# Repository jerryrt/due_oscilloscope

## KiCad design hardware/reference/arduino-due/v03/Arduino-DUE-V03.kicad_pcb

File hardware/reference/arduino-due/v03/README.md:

# Arduino Due V03 in KiCad

Open **[Arduino-DUE-V03.kicad_pro](Arduino-DUE-V03.kicad_pro)** in the
**KiCad 10 Project Manager**, then double-click `Arduino-DUE-V03.kicad_pcb`
in the project tree. You can also open the
[PCB](Arduino-DUE-V03.kicad_pcb) directly in the PCB Editor.
This is the working Due reference for the
owner's board. The alternate [V02g board](../v02g/DUE_V02g.kicad_pcb)
is retained for comparison.

The owner reported DUE R3 silkscreen, an AMS1117 regulator, a separate
inductor and a six-pin IC2 on 2026-11-01. That matches V03's power-supply
topology rather than V02g's IC5 module. The source specifies NCP1117 at
IC4; AMS1117 is a reported substitution, and IC2's exact marking is
unreported. [Observation record](../hardware-observations.json).

The source is `Arduino-DUE-V03`, retained as the original extracted EAGLE
[PCB](source/Arduino-DUE-V03.brd) and [schematic](source/Arduino-DUE-V03.sch).
Download ZIPs are intentionally omitted; their original names and hashes
remain in `sources.json`. Original publisher notices remain in these
source files. This is a local conversion, not an Arduino-published native
KiCad design.

| File | Purpose |
|---|---|
| `Arduino-DUE-V03.kicad_pro` | Project entry point and shared settings; initialized from KiCad 10.0.6's default template |
| `Arduino-DUE-V03.kicad_pcb` | Full converted PCB with embedded 2D footprints |
| `Arduino-DUE-V03.kicad_dru` | Importer-generated rules, not a fully verified project setup |
| `source/Arduino-DUE-V03.brd` | Unmodified EAGLE PCB |
| `source/Arduino-DUE-V03.sch` | Unmodified EAGLE schematic; no native KiCad schematic conversion |
| `sources.json` | Archive provenance, file hashes and layer-recovery notes |
| `import-report.json` | KiCad import statistics and diagnostics |
| `validation.json` | Source correspondence, reload and SVG-export checks |
| `import-board.py` / `check-board.py` | Recreate the board / verify it |

The PCB was originally imported in standalone mode, which did not create
a project file. The added `.kicad_pro` uses the same basename as the PCB
so KiCad opens them together. It starts with KiCad defaults; fabrication
rules and source net-class constraints have not been qualified. The
importer-generated `.kicad_dru` remains alongside it. Reimporting the board
preserves the project file and its settings.

The `.kicad_prl` file is local editor/view state and is ignored by Git.
There is still no native `.kicad_sch`; the original EAGLE schematic is
retained under `source/`. Creating a project file does not convert it.

KiCad **10.0.6** imports all **129 source components**, plus six footprints
for standalone mounting holes. All **591 source pad-to-net assignments**
match, and all component positions match within 0.000002 mm. Sixteen
references without numeric suffixes gain a trailing `0`; `validation.json`
records the mapping. Native load/save/reload and top-layer SVG export pass.
The import report contains no warnings or errors.

The importer puts seven unique straight-line restriction geometries on
an invalid `UNDEFINED` layer, merging front/back duplicates. The script
recovers all ten source lines as reference drawings: five front lines on
`User.1`, five back lines on `User.2`. **These lines do not enforce copper
keepouts.** Imported circular rule areas are separate. This board is for
reference and inspection; it has not been qualified for fabrication.
The owner's power-layout observations support using it as the reference;
full-board geometry and electrical continuity remain to be checked physically.

## The analog reference network (AREF, ADVREF)

Read from `Arduino-DUE-V03.kicad_pcb` (the same nets are in the EAGLE schematic).
`tests/test_due_reference_network.py` holds this table to the PCB. It is the
converted board file, not the owner's physical board: check continuity before
reworking anything.

| Net | Pads on it |
|---|---|
| `AREF` | BR1 pad 1, and the AREF header pin (header `PWMH0` pad 8). Nothing else |
| `AVREFL` | BR1 pad 2, JR1 pad 2, C34 (100 nF to ground), L3 pad 1 |
| `AVREF` | L3 pad 2, C19 (100 nF to ground), the SAM3X's ADVREF pin (U1 pad 75) |
| `+3V3` | BR1 pad 3, JR1 pad 1, and the rest of the 3.3 V rail |

L3 is the ferrite bead `MH2029-300Y` in an 0805, which by its part number is 30
ohms at 100 MHz *(check)*. BR1 is the 0402 three-pad jumper `J0402`, not mounted,
on the top copper layer, with 1.3 mm between pad centres. JR1 is a 0 ohm 0402 on
the top layer.

**As shipped,** JR1 joins 3.3 V to `AVREFL`, and the converters' reference is
3.3 V through L3 and C19. The AREF header pin goes nowhere.

**To drive ADVREF from outside,** in this order. The AFE requirement decided D6 as
measure only, so this is a later option, not part of the AFE's version 1:

1. Remove JR1.
2. Bridge BR1 pads 1 and 2: a 0402 0 ohm part fits the footprint, and a solder
   bridge across the gap of 0.6 mm (pads 0.7 mm long on a 1.3 mm pitch) also reaches, with less margin. The AREF header pin is then
   `AVREFL`, and ADVREF follows it through L3.
3. Check continuity before power: AREF to ADVREF closed, 3.3 V to AREF open.

**The order matters.** With BR1 pads 1 and 2 bridged and JR1 still fitted, the
AREF pin is tied to the 3.3 V rail through 0 ohms, and whatever drives AREF is
shorted to it.

Both parts are on the top layer under where a shield sits, so the rework is done
before stacking. A shield reaches AREF through the stacking header, with no jumper
wire. On the Due it is header `PWMH0` pad 8 in this board file, the AREF pin of
the header.

**The load an external reference sees:** C34, then the bead, then C19, about 200 nF,
before any trace and header contact on the shield. It has to be stable with that
and with the converters' switching load, a datasheet check. A Due reworked this way
and run without a reference connected has a floating ADVREF.

**Without touching JR1,** or with a way back:

- **Do not drive ADVREF.** Leave the Due stock and let the ADC read the shield's
  reference as an input. That gives each board's absolute gain and its drift to the
  host, and needs no rework; it does not quieten ADVREF.
- **Use BR1 as the selector it was drawn as.** Remove JR1 once, then bridge BR1 pads
  2 and 3 for the stock behaviour (3.3 V to AVREFL, the same connection JR1 made) or
  pads 1 and 2 for an external reference. With 2 and 3 bridged the Due works alone
  and a shield driving AREF cannot hurt it. With 1 and 2 bridged and no reference
  connected, ADVREF has no source, and the converters do not work.
- **Rework one Due only,** and keep it with the shield. The others stay stock, which
  also gives a control.

Removing JR1 and leaving BR1 open does leave ADVREF with no source: the only paths
into `AVREFL` and `AVREF` are JR1 and BR1.

Not established by the board file: the highest ADVREF the SAM3X accepts against its
analog supply `VDDANA` (3.3 V through a second bead, L1), a datasheet check.

## 3D view

**119 component models are assigned.** The owner-supplied STEP assembly provides 18:
the MCU, both USB connectors, barrel jack, main headers, debug/SPI/ICSP/JTAG
headers, two large capacitors and reset switch. Another 91 assignments use
standard KiCad package bodies, and 10 use documented simplified bodies for
the fuses, power inductor, small crystal, ESD protectors and erase switch.
Reopen the PCB from disk
and choose **View -> 3D Viewer** (Option+3 on macOS).

The owner reported on 2026-11-01 that the initial 18-model preview passed a first visual
inspection and matches the physical board well. This is an overall visual
check, with no dimensional measurements or electrical checks reported.
The expanded population shown above has not yet been inspected by the owner.
[Observation record](../hardware-observations.json).

The source board is 101.6 x 53.34 mm and its six mounting-hole centers
match V03's EAGLE source within 0.000006 mm. Bodies retain the source's
small placement offsets, including the MCU's 0.020 mm center offset.
These are CAD correspondence checks, not physical measurements. Connector
heights, detailed pin fit and component substitutions are not qualified.

The supplied assembly's PCB slab is excluded so the native PCB and copper
remain visible. Its oversized LED bodies and generic capacitor bodies are
also excluded; standard package and simplified bodies now fill the small
components. Four bare fiducials and six source NM items (including BR1)
remain without bodies. Generic
plastic/metal colors improve visibility; they do not identify actual
materials or capacitor values. New package models align polarity and pin-1
to the source pad layout; installed markings and body heights remain
unqualified. In particular the tantalum B-case bodies and erase-switch
height are approximations. The
[model preparation/alignment record](../models/README.md) lists all assets
and exclusions. [Attachment evidence](models-3d.json) confirms every
non-model line of the PCB file is unchanged.

`attach-models.py` restores these assignments without rewriting the native
geometry. `import-board.py` also reapplies them when `models/alignment.json`
is present. The checker verifies all assigned file paths and hashes.

From the repository root, recreate the conversion (overwrites this V03
PCB and its import/provenance records):

```sh
python3 hardware/reference/arduino-due/v03/import-board.py
```

Then verify with KiCad's bundled Python on this Mac:

```sh
/Applications/KiCad/KiCad.app/Contents/Frameworks/Python.framework/Versions/3.9/bin/python3 hardware/reference/arduino-due/v03/check-board.py
```

On another system use Python with KiCad 10's `pcbnew` module available.
Set `KICAD_CLI` if the executable is not on PATH or at the default macOS
location. The checker writes `validation.json` and uses temporary files
for its reload and SVG checks.

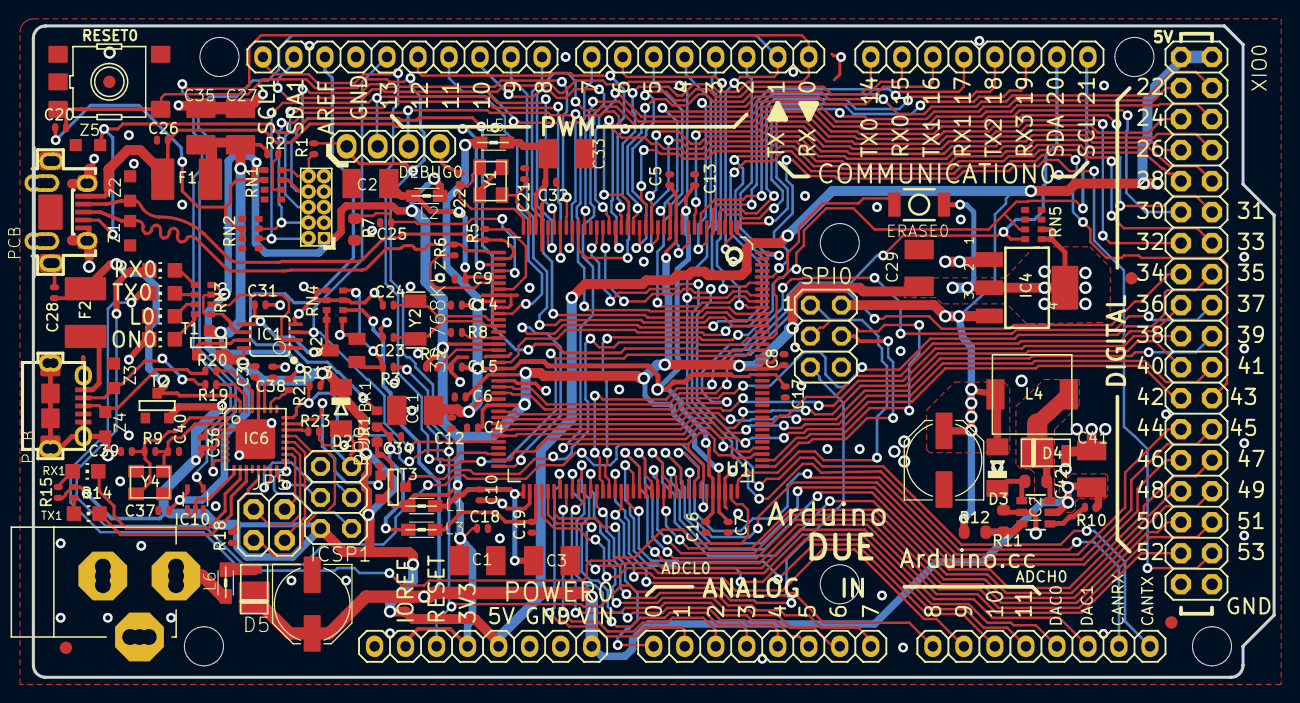
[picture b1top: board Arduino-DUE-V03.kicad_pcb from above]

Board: 2 copper layers, 101.6 x 53.3 mm, 135 parts (0 on the bottom side), 150 nets.

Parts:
ADCH0: 8x1F-H8.5; 1X08
ADCL0: 8x1F-H8.5; 1X08
BR1: NM; J0402
C1, C2, C3, C11, C27, C29, C33, C35, C41: 10u; SMC_B
C4, C5, C6, C7, C8, C9, C10, C12, C13, C14, C15, C16, C17, C18, C19, C28, C30, C31, C32, C34, C36, C37: 100n; C0402
C20, C26: 10n; C0402
C21, C22, C25, C39, C40: 22p; C0402
C23, C24: 22pF_NM; C0402
C38: 1u; C0402
C42: 10n; C0603-ROUND
COMMUNICATION0: 8x1F-H8.5; 1X08
D2, D3: CD1206-S01575; MINIMELF
D4, D5: SS1P3L; DO220AAL
DEBUG0: STRIP 4x1V M; 1X04
ERASE0: SMD_157SW
F1, F2: MF-MSMF050-2 500mA; L1812
FID1, FID2, FID3, FID4: FIDUCIALMOUNT; FIDUCIA-MOUNT
IC1: LMV358IDGKR; MSOP08
IC2: LM2734Y; SOT23-6
IC4: NCP1117ST33T3G -3V3; SOT223
IC6: ATMEGA16U2-MU; MLF32
IC10: 74LVC1G125DCK; SC70-5
ICSP1: 3x2M; 2X03
J3: USB-MICRO B; CON2_USB_MICRO_B_AT
JP5: 2x2M - NM; 2X02
JR1: 0R; R0402
JTAG0: PINHEAD_2X05_127
L0: YELLOW; CHIP-LED0805
L1, L2, L3, L5, L6: MH2029-300Y; 0805
L4: 10u SRR0604-100ML; SRR0604
ON0: GREEN; CHIP-LED0805
PC1, PC2: 47u; PANASONIC_D
POWER0: 8x1F-H8.5; 1X08
PWMH0: 10x1F-H8.5; 1X10
PWML0: 8x1F-H8.5; 1X08
Q2: BC847BSMD; SOT23
R1: 0R; R0402
R2, R13, R18, R99: 10K; R0402
R3, R14, R15, R21, R23: 1K; R0402
R4: 100K; R0402
R5, R6: 39R 1%; R0402
R7: 6k8 1%; R0603-ROUND
R8: 0R_NM; R0402
R9: 1M_NM; R0402
R10: 10k; R0402
R11: 10K; R0603-ROUND
R12: 52K3; R0603-ROUND
R19, R20: 22R; R0402
RESET0: TS42
RN1, RN2, RN4: 100K; CAT16
RN3: 1k; CAY16
RN5: 1K5; CAT16
RX0, RX1: YELLOW; CHIP-LED0805
SPI0: 3x2M; 2X03
T1, T2, T3: FDN340P; SOT-23
TX0, TX1: YELLOW; CHIP-LED0805
U1: ATSAM3X8EA-AU; LQFP144
UNK_HOLE_0: dummyfp0
UNK_HOLE_1: dummyfp1
UNK_HOLE_2: dummyfp2
UNK_HOLE_3: dummyfp3
UNK_HOLE_4: dummyfp4
UNK_HOLE_5: dummyfp5
USB1: MICRO-USB-AB1; MCR-AB1-S-RA-SMT
X2: POWERSUPPLY_DC21MMX; POWERSUPPLY_DC-21MM
XIO0: 18x2F-H8.5; 2X18
Y1: 12MHz KX-7 20pF; CRYSTAL-3.2-2.5
Y2: 32.768Khz; RESONATOR_EPSON_FC_145
Y4: 16MHz KX-7 20pF; CRYSTAL-3.2-2.5
Z1, Z2, Z3, Z4, Z5: CG0603MLC-05E; CT_CN0603

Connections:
8PB4: IC6.18, JP5.1
8PB5: IC6.19, JP5.3
8PB6: IC6.20, JP5.2
8PB7: IC6.21, JP5.4
16U2-TX: IC6.9, IC10.1, IC10.2
+3V3: BR1.3, C1.+, C4.2, C5.2, C6.2, C7.2, C8.2, C18.2, C20.2, C29.+, C37.1, ERASE0.1, IC1.6, IC4.2, IC4.4, IC10.5, JR1.1, JTAG0.1, L1.1, L2.1, POWER0.2, POWER0.4, R4.2, R99.2, RN1.5, RN1.6, RN2.2, RN2.3, RN3.5, RN3.7, RN3.8, RN5.1, RN5.2, T3.2, U1.11, U1.52, U1.57, U1.62, U1.105, U1.125
+5V: C30.2, C36.1, D2.C, D3.A, IC1.8, IC4.3, IC6.4, IC6.32, ICSP1.2, L4.P$2, PC2.+, POWER0.5, R12.1, R13.2, R14.1, R15.1, SPI0.2, T1.2, T2.2, XIO0.1, XIO0.2
AD0: ADCL0.1, U1.78
AD1: ADCL0.2, U1.79
AD2: ADCL0.3, U1.80
AD3: ADCL0.4, U1.81
AD4: ADCL0.5, U1.82
AD5: ADCL0.6, U1.83
AD6: ADCL0.7, U1.84
AD7: ADCL0.8, U1.85
AD8: ADCH0.1, U1.88
AD9: ADCH0.2, U1.89
AD10: ADCH0.3, U1.90
AD11(TXD3): ADCH0.4, U1.91
AD14(RXD3): U1.92, XIO0.33
AREF: BR1.1, PWMH0.8
AVREF: C19.2, L3.2, U1.75
AVREFL: BR1.2, C34.2, JR1.2, L3.1
BD+: J3.P3, R20.2, Z4.2
BD-: J3.P2, R19.2, Z3.2
BOOST: C42.1, D3.C, IC2.1
CANRX0: ADCH0.7, U1.24
CANTX0: ADCH0.8, U1.23
CANTX1/IO: U1.140, XIO0.34
CMP: C31.2, IC1.5, Q2.3, RN4.3, RN4.4
D+: R6.1, U1.37, USB1.3, Z1.1
D-: R5.1, U1.38, USB1.2, Z2.1
DAC0(CANRX1): ADCH0.5, U1.76
DAC1: ADCH0.6, U1.77
DTR: IC6.13, R18.1
EN: IC2.4, R10.2
ERASE_CMD: IC6.23, R99.1, T3.3
ERASE_S: ERASE0.2, T3.1, U1.130
FB: IC2.3, R11.1, R12.2
GATE_CMD: IC1.7, T1.3
GND: C1.-, C2.-, C3.-, C4.1, C5.1, C6.1, C7.1, C8.1, C9.1, C10.1, C11.-, C12.1, C13.1, C14.1, C15.1, C16.1, C17.1, C18.1, C19.1, C21.2, C22.2, C23.2, C24.2, C25.2, C26.2, C27.-, C28.2, C29.-, C30.1, C31.1, C32.1, C33.-, C34.1, C35.-, C36.2, C37.2, C38.2, C39.2, C40.2, C41.-, D4.P$2, DEBUG0.1, IC1.4, IC2.2, IC4.1, IC6.3, IC6.28, IC6.33, IC10.3, ICSP1.6, J3.P5, J3.P$1, J3.P$2, J3.P$3, J3.P$4, J3.P$5, J3.P$6, J3.P$7, J3.P$8, J3.S1, J3.S2, J3.S3, J3.S4, J3.S5, J3.S6, JTAG0.3, JTAG0.5, JTAG0.9, L0.C, ON0.C, PC1.-, PC2.-, POWER0.6, POWER0.7, PWMH0.7, Q2.2, R2.1, R7.1, R8.1, R11.2, R18.2, RESET0.1, RESET0.2, RN1.1, RN1.2, RN1.7, RN1.8, RN2.1, RN2.4, RN2.5, RN2.8, RN4.1, RN4.2, RN4.5, RN4.7, SPI0.6, T2.3, U1.12, U1.33, U1.44, U1.46, U1.54, U1.58, U1.74, U1.106, U1.126, USB1.5, USB1.P$1, USB1.P$2, USB1.P$3, USB1.P$4, USB1.P$5, USB1.P$6, USB1.P$7, USB1.P$8, USB1.P$9, USB1.P$10, USB1.P$11, USB1.S1, USB1.S2, USB1.S3, USB1.S4, X2.1, X2.3, XIO0.35, XIO0.36, Y1.2, Y1.4, Y4.2, Y4.4, Z1.2, Z2.2, Z3.1, Z4.1, Z5.1
JTAG_RESET: JTAG0.10, R1.1, RN1.4
JTAG_TCK: DEBUG0.2, JTAG0.4, RN2.7, U1.28
JTAG_TDI: JTAG0.8, RN1.3, U1.29
JTAG_TDO: JTAG0.6, U1.30
JTAG_TMS: DEBUG0.3, JTAG0.2, RN2.6, U1.31
L13: IC1.1, IC1.2, RN3.6
MASTER-RESET: C20.1, DEBUG0.4, POWER0.3, R1.2, R23.2, RESET0.3, RESET0.4, SPI0.5, U1.47
MISO: SPI0.1, U1.108
MISO2: IC6.17, ICSP1.1
MOSI: SPI0.4, U1.109
MOSI2: IC6.16, ICSP1.4
unnamed: IC6.26, R21.1
unnamed: L0.A, RN3.3
unnamed: ON0.A, RN3.4
unnamed: R15.2, RX1.A
unnamed: R8.2, U1.51
unnamed: Q2.1, R3.2, RN4.8
unnamed: R4.1, U1.53
unnamed: D5.P$2, L6.1
unnamed: R5.2, U1.43
unnamed: R6.2, U1.42
unnamed: R14.2, TX1.A
unnamed: RN3.1, RX0.A
unnamed: RN3.2, TX0.A
PIN22: U1.1, XIO0.3
PIN23: U1.7, XIO0.4
PIN24: U1.8, XIO0.5
PIN25: U1.13, XIO0.6
PIN26: U1.14, XIO0.7
PIN27: U1.15, XIO0.8
PIN28: U1.16, XIO0.9
PIN29: U1.19, XIO0.10
PIN30: U1.22, XIO0.11
PIN31: U1.26, XIO0.12
PIN32: U1.32, XIO0.13
PIN33: U1.55, XIO0.14
PIN34: U1.59, XIO0.15
PIN35: U1.60, XIO0.16
PIN36: U1.116, XIO0.17
PIN37: U1.63, XIO0.18
PIN38: U1.64, XIO0.19
PIN39: U1.65, XIO0.20
PIN40: U1.66, XIO0.21
PIN41: U1.67, XIO0.22
PIN42: U1.71, XIO0.23
PIN43: U1.72, XIO0.24
PIN44: U1.101, XIO0.25
PIN45: U1.100, XIO0.26
PIN46: U1.99, XIO0.27
PIN47: U1.98, XIO0.28
PIN48: U1.97, XIO0.29
PIN49: U1.96, XIO0.30
PIN50: U1.95, XIO0.31
PIN51: U1.94, XIO0.32
PWM2: PWML0.3, U1.144
PWM3: PWML0.4, U1.139
PWM5: PWML0.6, U1.136
PWM6: PWML0.7, U1.135
PWM7: PWML0.8, U1.134
PWM8: PWMH0.1, U1.133
PWM9: PWMH0.2, U1.132
PWM11: PWMH0.4, U1.20
PWM12: PWMH0.5, U1.21
PWM13: IC1.3, PWMH0.6, U1.68
RD+: IC6.29, R20.1
RD-: IC6.30, R19.1
RESET2: D2.A, IC6.24, ICSP1.5, R13.1
RESET_CMD: IC6.22, R23.1
RX: IC10.4, PWML0.1, U1.27
RXD0: COMMUNICATION0.2, U1.18
RXD1: COMMUNICATION0.4, U1.5
RXD2: COMMUNICATION0.6, U1.3
RXL: RX0.C, U1.103
RXL-U2: IC6.10, RX1.C
SCK2: IC6.15, ICSP1.3
SCL0-3: COMMUNICATION0.8, RN5.7, U1.87
SCL1: PWMH0.10, U1.70
SDA0-3: COMMUNICATION0.7, RN5.8, U1.86
SDA1: PWMH0.9, U1.9
SPCK: SPI0.3, U1.110
SS0/PWM10: PWMH0.3, U1.102, U1.111
SS1/PWM4: PWML0.5, U1.112, U1.137
SW: C42.2, D4.P$1, IC2.6, L4.P$1
TX: IC6.8, PWML0.2, U1.2
TXD0: COMMUNICATION0.1, U1.17
TXD1: COMMUNICATION0.3, U1.6
TXD2: COMMUNICATION0.5, U1.4
TXL: TX0.C, U1.107
TXL-U2: IC6.11, TX1.C
UOTGID: U1.129, USB1.4, Z5.2
UOTGVBOF: R3.1, U1.128
USBVCC: C27.+, C35.+, F1.1, R2.2, R21.2, T1.1
USBVCCU2: C28.1, F2.1, IC6.31, T2.1
VBG: C25.1, R7.2, U1.40
VDDANA: C3.+, C10.2, L1.2, U1.73
VDDOUT: C11.+, C12.2, C13.2, C14.2, C15.2, C16.2, C17.2, L5.1, U1.10, U1.45, U1.56, U1.61, U1.104, U1.124
VDDOUTMI: C2.+, C9.2, L2.2, U1.41
VDDPLL: C32.2, C33.+, L5.2, U1.34
VIN: C41.+, D5.P$1, IC2.5, PC1.+, POWER0.8, R10.1, RN4.6
VIN+: L6.2, X2.2
VUCAP: C38.1, IC6.27
XIN: C22.1, U1.36, Y1.1
XIN32: C24.1, U1.48, Y2.P$2
XOUT: C21.1, U1.35, Y1.3
XOUT32: C23.1, U1.49, Y2.P$1
XT1: C39.1, IC6.1, R9.1, Y4.1
XT2: C40.1, IC6.2, R9.2, Y4.3
XUSB: C26.1, F1.2, U1.39, USB1.1
XVCC: F2.2, J3.P1
